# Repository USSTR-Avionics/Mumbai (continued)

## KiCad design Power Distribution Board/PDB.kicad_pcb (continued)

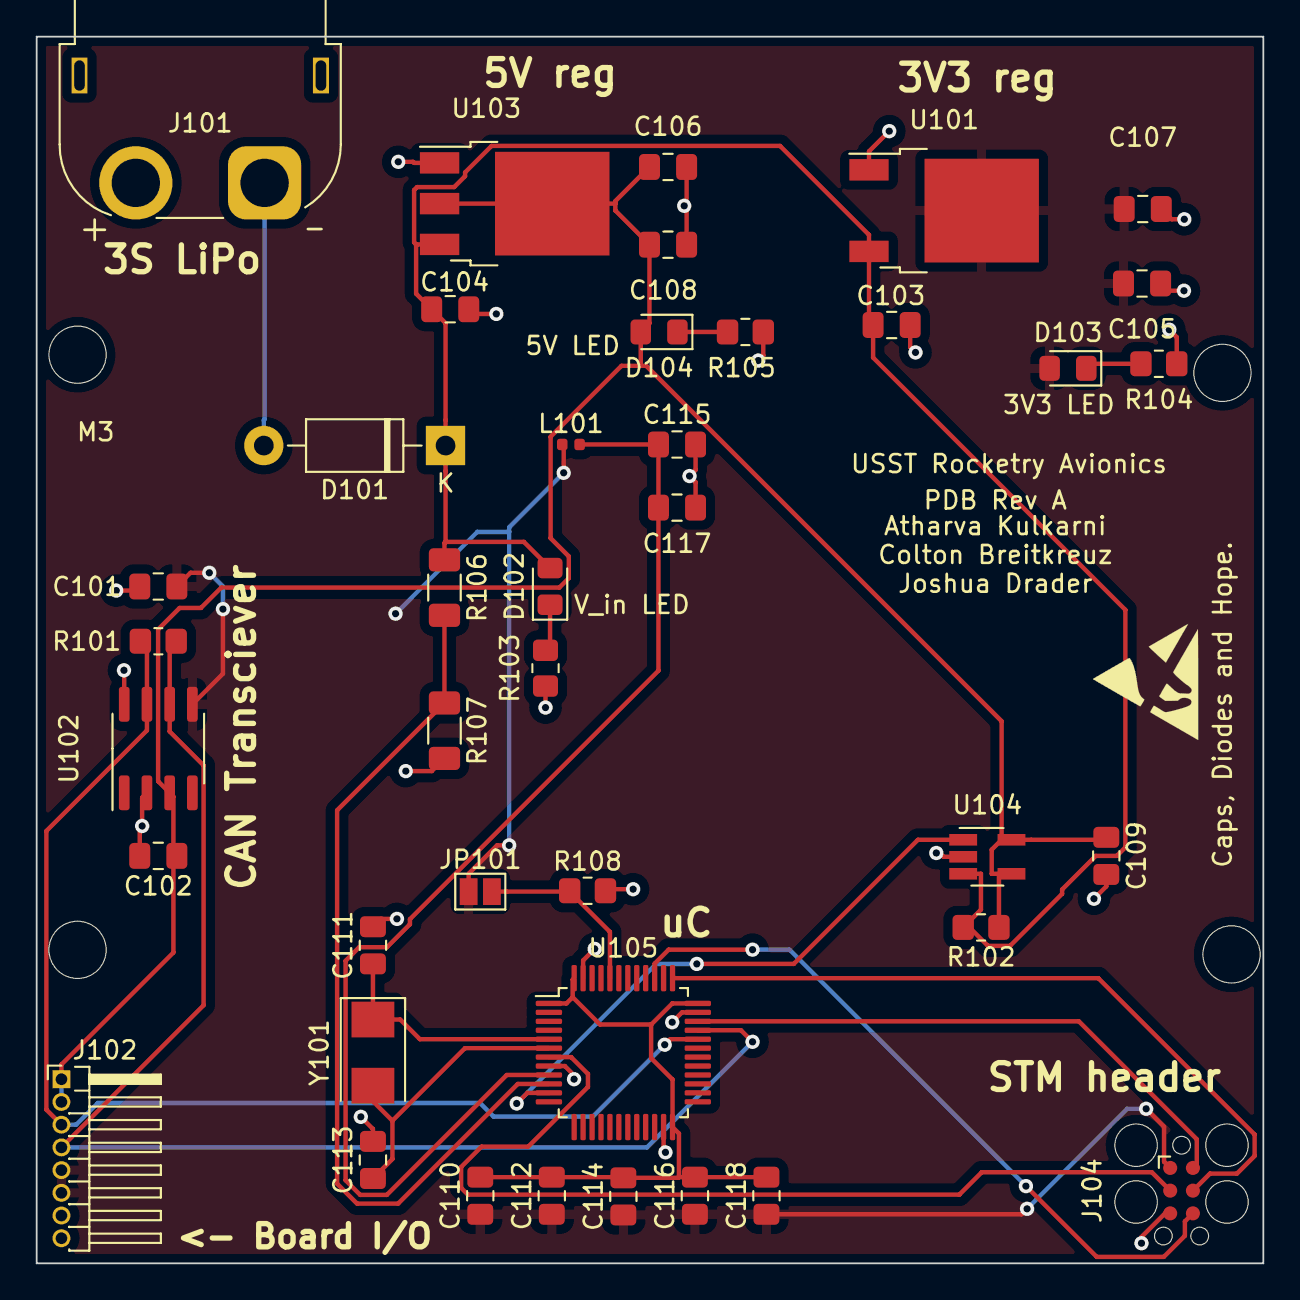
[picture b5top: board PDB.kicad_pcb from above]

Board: 2 copper layers, 68.6 x 68.6 mm, 42 parts (0 on the bottom side), 21 nets.

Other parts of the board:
M3: MountingHole_3.2mm_M3

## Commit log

2023-03-26 moved repos here
2023-03-28 changed file names
2023-04-02 added gitignore
2023-04-02 Initial LoRa commit
2023-04-02 RF initial commit
2023-04-05 RF: initial commit CC1110 and Balun
2023-04-09 Updated GPS Board Schematic, still need to remake board
2023-04-15 added external memory
2023-04-15 RF: Push for schematic capture review version 1.0
2023-04-15 RF: added pdf
2023-04-16 misc: sync
2023-04-16 fc: inital work
2023-04-17 added image
2023-04-17 fc: init design
2023-04-17 removed changes to allow a PR
2023-04-19 fc: restarted with new uc
2023-04-19 added standard connector and some initial layout
2023-04-19 added standard suck
2023-04-21 added power and ground
2023-04-26 working on functional requirements
2023-04-28 updated document
2023-04-29 updated requirements to be high level
2023-04-30 added new led BOM
2023-05-03 added rfc process diagram
2023-05-12 asdf
2023-05-27 Created flightComputer.cpp, readme.md, and staticVariables.h -created most of the functions that are needed for the flight computer and created the base state machine -populated the enum flightStates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
2023-06-25 added flight computer files
2023-07-24 layout rev 1.0
2023-07-24 silkscreen
2023-07-24 connections ting
2023-08-26 added module templates
2023-09-02 Updated STM32F405RGT6 template
2023-09-03 Added flight comp V2 STM, KX134, BMP280, MCP2562
2023-09-04 added more sensors to flight computer v2
2023-09-04 more flgiht computer v2 updates
2023-09-05 finalized schematic, added datasheets, and pdf of schematic
2023-09-09 updated pcb
2023-10-14 updated v2 flight computer
2023-10-20 changed new flight computer scl resistors
